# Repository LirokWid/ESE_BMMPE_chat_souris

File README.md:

# ESE_BMMPE_chat_souris

Ce project a pour but de développer un robot qui joue à chat avec d'autres robots, il embarque un PCB custom avec un STM32G070. Le projet est développé avec freeRTOS.

Le pcb permet la connection de :
- 2 moteurs DC
- 2 encodeurs
- 1 module Bluetooth
- 1 lidar ydlidar x4
- 4 capteurs de touche
- 2 capteurs de vide
- 1 centrale inertielle

Membres :

- M PICHERY
- B RODIER
- M VAN DE MOOSDJIK
- P.-E. RETAUX

## Organisation du code

Le code fonctionne en modules contenus dans le dossier `drivers`.
Les dossiers sont organisés de la manière suivante :

- `CONTROL` :
Gère la logique de contrôle du robot. Il génère les signaux de commande pour les moteurs et les encodeurs.
- `HC-05` :
Api de communication avec le module Bluetooth HC-05.
- `IT` :
Gère les interruptions du microcontrôleur.
- `LIDAR` : 
Routine d'acquisition des données du lidar.
- `MOTOR` :
Gère les moteurs et les encodeurs.
- `MPU6050` :
Api de communication avec la centrale inertielle MPU6050.
- `PARAMS` :
Gère les paramètres du robot.
- `SYS_HELPER` :
Fonctions utilitaires pour le système.
- `UART` :
Fonctions de communication UART.

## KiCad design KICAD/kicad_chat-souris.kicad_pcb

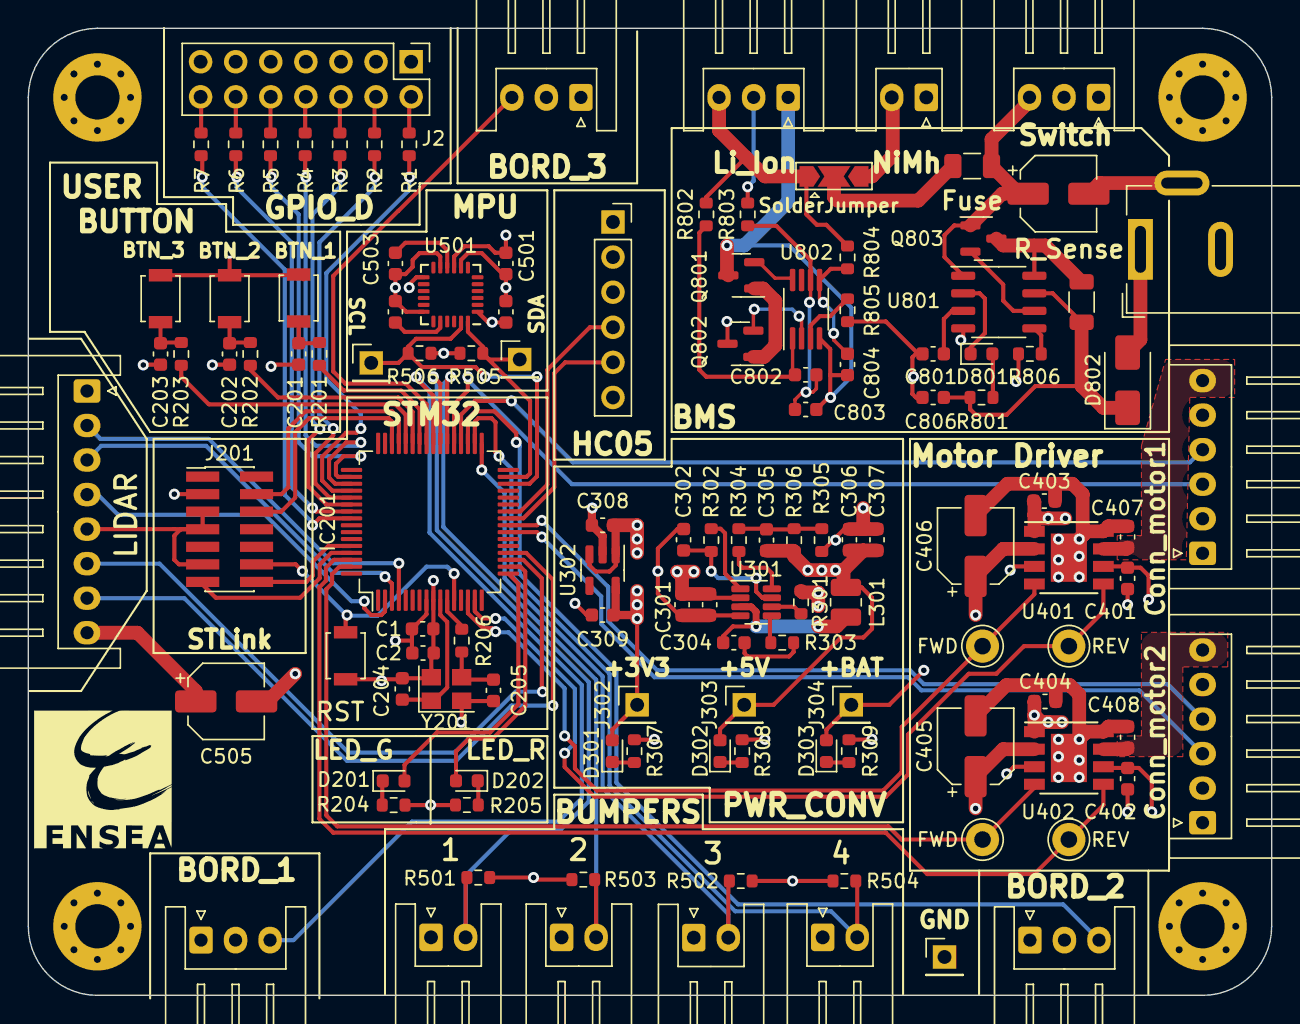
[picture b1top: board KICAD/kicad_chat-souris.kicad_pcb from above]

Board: 4 copper layers, 90.0 x 70.0 mm, 124 parts (1 on the bottom side), 98 nets.

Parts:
C1: 470n; C_0603_1608Metric
C2: 4.7µ; C_0603_1608Metric
C201, C202, C203, C302, C303, C304, C305, C503: 0.1uF; C_0603_1608Metric
C204, C205: 10pF; C_0603_1608Metric
C301, C306, C307: 22uF; C_0603_1608Metric
C308, C309, C401, C402: 1uF; C_0603_1608Metric
C403, C404, C407, C408: 47nF; C_0603_1608Metric
C405, C406: 10uF; CP_Elec_5x5.4
C501: 0.01nF; C_0603_1608Metric
C502: 0.01uF; C_0603_1608Metric
C504: 2.2nF; C_0603_1608Metric
C505: 4.7µ; CP_Elec_5x5.4
C801: 0.1µF; C_0603_1608Metric
C802, C803: 100n; C_0603_1608Metric
C804: 100nF; C_0603_1608Metric
C805: 10µ; CP_Elec_5x5.4
C806: 1µF; C_0603_1608Metric
D201: led_green; LED_0603_1608Metric
D202: led_red; LED_0603_1608Metric
D301, D302, D303: blue; LED_0603_1608Metric
D801: LED; LED_0603_1608Metric
D802: D_Schottky; D_SMA
F801: MF-NSML150/12-2; Fuse_1206_3216Metric
FWD: Pin_D1.0mm_L10.0mm_LooseFit
FWD#2: Pin_D1.0mm_L10.0mm_LooseFit
G1: LOGO; CHAT_SOURIE
IC201: STM32G070RBT6; LQFP-64_10x10mm_P0.5mm
J2: Conn_02x07_Counter_Clockwise; PinHeader_2x07_P2.54mm_Vertical
J201: ST/link connector; PinHeader_2x07_P1.27mm_Vertical_SMD
J301: power switch JST; JST_XH_S3B-XH-A_1x03_P2.50mm_Horizontal
J302: 3V3; PinHeader_1x01_P2.54mm_Vertical
J303: 5V; PinHeader_1x01_P2.54mm_Vertical
J304: V_BAT; PinHeader_1x01_P2.54mm_Vertical
J305: GND; PinHeader_1x01_P2.54mm_Vertical
J401: Conn_motor1; JST_XH_S6B-XH-A_1x06_P2.50mm_Horizontal
J402: Conn_motor2; JST_XH_S6B-XH-A_1x06_P2.50mm_Horizontal
J503: Conn_lidar; JST_XH_S8B-XH-A_1x08_P2.50mm_Horizontal
J504: Conn_Bmp_3; JST_XH_S2B-XH-A_1x02_P2.50mm_Horizontal
J505: Conn_Bmp_4; JST_XH_S2B-XH-A_1x02_P2.50mm_Horizontal
J506: SDA; PinHeader_1x01_P2.54mm_Vertical
J507: SCL; PinHeader_1x01_P2.54mm_Vertical
J601: Conn_bord1; JST_XH_S3B-XH-A_1x03_P2.50mm_Horizontal
J602: Conn_bord2; JST_XH_S3B-XH-A_1x03_P2.50mm_Horizontal
J801: 694102303002; BarrelJack_Wuerth_6941xx301002
J802: NiMH_Conn; JST_XH_S2B-XH-A_1x02_P2.50mm_Horizontal
J803: Li-Ion_Conn; JST_XH_S3B-XH-A_1x03_P2.50mm_Horizontal
JP801: SolderJumper; SolderJumper-3_P2.0mm_Open_TrianglePad1.0x1.5mm
L301: 4.7uH; L_1008_2520Metric
Q801, Q802: NMOS; SOT-23
Q803: PMOS; SOT-23
R1, R2, R3, R4, R5, R6, R7: R_Small; R_0603_1608Metric
R201, R202, R203: 20k; R_0603_1608Metric
R204: 5; R_0603_1608Metric
R205: 65; R_0603_1608Metric
R206: 10; R_0603_1608Metric
R301, R501, R502, R503, R504: 10k; R_0603_1608Metric
R302: 100k; R_0603_1608Metric
R303: 20; R_0603_1608Metric
R304: 16k; R_0603_1608Metric
R305: 7.68k; R_0603_1608Metric
R306: 40.2k; R_0603_1608Metric
R307, R802, R803, R804: 100; R_0603_1608Metric
R308: 50; R_0603_1608Metric
R309: 270; R_0603_1608Metric
R505, R506: 4.7k; R_0603_1608Metric
R801, R805: 2k; R_0603_1608Metric
R806: 19.6k; R_0603_1608Metric
REV: Pin_D1.0mm_L10.0mm_LooseFit
REV#2: Pin_D1.0mm_L10.0mm_LooseFit
R_SENSE801: 0.2; R_1206_3216Metric
SW201: RESET; SW_SPST_B3U-1000P
SW202: BTN_1; SW_SPST_B3U-1000P
SW203: BTN_2; SW_SPST_B3U-1000P
SW204: BTN_3; SW_SPST_B3U-1000P
U301: MP1475; SOT-23-8
U302: MIC5317-3.3v; SOT-23-5
U401: ZXBM5210-S_1; Diodes_SO-8EP
U402: ZXBM5210-S_2; Diodes_SO-8EP
U501: MPU-6050; InvenSense_QFN-24_4x4mm_P0.5mm
U701: PinSocket_1x06_P2.54mm_Vertical
U801: LTC1731ES8-8_4; SO-8_3.9x4.9mm_P1.27mm
U802: MSOP-8_3x3mm_P0.65mm
Y201: Crystal; Crystal_SMD_3225-4Pin_3.2x2.5mm
locked: Conn_Bmp_1; JST_XH_S2B-XH-A_1x02_P2.50mm_Horizontal
locked#2: Conn_Bmp_2; JST_XH_S2B-XH-A_1x02_P2.50mm_Horizontal
locked#3: Conn_bord3; JST_XH_S3B-XH-A_1x03_P2.50mm_Horizontal

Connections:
+3V3: C1.1, C2.1, C309.1, C401.1, C402.1, C501.1, C502.1, D301.2 (A), IC201.8 (VDD/VDDA), J201.3, J302.1, J401.5, J402.5, J601.2, J602.2, R501.2, R502.2, R503.2, R504.2, R505.2, R506.2, U302.5 (VOUT), U401.3 (VDD), U401.6 (VREF), U402.3 (VDD), U402.6 (VREF), U501.8 (VLOGIC), U501.13 (VDD), locked#3.2
+5V: C305.2, C306.1, C307.1, C308.1, C505.1, D302.2 (A), J303.1, J503.8, L301.2, R306.2, U302.1 (VIN), U302.3 (EN), U701.2 (Vcc(5v))
+BATT: C301.1, C303.1, C405.1, C406.1, D303.2 (A), J301.2, J304.1, R301.1, U301.2 (IN), U401.2 (VM), U402.2 (VM)
/Alimentation/BMS/Secu_Dout: Q801.2 (G), U802.8 (Dout)
/Alimentation/BMS/Secu_Sense: C804.1, R804.2, U802.5 (Sense)
/Alimentation/BMS/Secu_V-: R805.1, U802.3 (V-)
/Alimentation/BMS/Secu_VDD: C802.1, R802.1, U802.1 (VDD)
/Alimentation/BMS/Secu_Vc: C802.2, C803.1, R803.1, U802.6 (Vc)
/Alimentation/BMS/Secu_Vout: Q802.2 (G), U802.2 (Cout)
/Alimentation/BUCK_FB: R304.1, U301.8 (FB)
/Alimentation/BUCK_SW: C304.2, L301.1, U301.3 (SW)
/Drivers and motors connectors/ENCODER_1_A: IC201.37 (PA9), J401.3
/Drivers and motors connectors/ENCODER_1_B: IC201.36 (PA8), J401.4
/Drivers and motors connectors/ENCODER_2_A: IC201.23 (PA6), J402.3
/Drivers and motors connectors/ENCODER_2_B: IC201.24 (PA7), J402.4
/Drivers and motors connectors/MOT1_OUT1: C403.1, J401.1, U401.1 (OUT1)
/Drivers and motors connectors/MOT1_OUT2: C407.1, J401.6, U401.7 (OUT2)
/Drivers and motors connectors/MOT2_OUT1: C404.1, J402.1, U402.1 (OUT1)
/Drivers and motors connectors/MOT2_OUT2: C408.1, J402.6, U402.7 (OUT2)
/Drivers and motors connectors/MOTOR_1_FWD: FWD#2.1, IC201.14 (PC1), U401.4 (FWD)
/Drivers and motors connectors/MOTOR_1_REV: IC201.15 (PC2), REV#2.1, U401.5 (REV)
/Drivers and motors connectors/MOTOR_2_FWD: FWD.1, IC201.63 (PB9), U402.4 (FWD)
/Drivers and motors connectors/MOTOR_2_REV: IC201.62 (PB8), REV.1, U402.5 (REV)
/STM32/BTN_1: IC201.42 (PA10), R201.1
/STM32/BTN_2: IC201.43 (PA11_[PA9]), R202.1
/STM32/BTN_3: IC201.44 (PA12_[PA10]), R203.1
/STM32/Bordure_1: IC201.40 (PD8), J601.3
/STM32/Bordure_2: IC201.41 (PD9), J602.3
/STM32/Bordure_3: IC201.35 (PB15), locked#3.3
/STM32/Bumper_1: IC201.39 (PC7), R501.1, locked.2
/STM32/Bumper_2: IC201.38 (PC6), J504.2, R503.1
/STM32/Bumper_3: IC201.33 (PB13), R502.1, locked#2.2
/STM32/Bumper_4: IC201.34 (PB14), J505.2, R504.1
/STM32/I2C_SCL: IC201.30 (PB10), J507.1, R506.1, U501.23 (SCL)
/STM32/I2C_SDA: IC201.31 (PB11), J506.1, R505.1, U501.24 (SDA)
/STM32/LIDAR_MESURE_ENABLE: IC201.3 (PC13), J503.3
/STM32/LIDAR_MOTOR_ENABLE: IC201.4 (PC14-OSC32_IN), J503.2
/STM32/LIDAR_PWM: IC201.2 (PC12), J503.4
/STM32/NRST: IC201.12 (NRST), J201.12, SW201.2 (B)
/STM32/OSC_IN: C204.1, IC201.10 (PF0-OSC_IN), Y201.1
/STM32/OSC_OUT: IC201.11 (PF1-OSC_OUT), R206.1
/STM32/PD0: IC201.50 (PD0), R5.1
/STM32/PD1: IC201.51 (PD1), R4.1
/STM32/PD2: IC201.52 (PD2), R1.1
/STM32/PD3: IC201.53 (PD3), R2.1
/STM32/PD4: IC201.54 (PD4), R3.1
/STM32/PD5: IC201.55 (PD5), R6.1
/STM32/PD6: IC201.56 (PD6), R7.1
/STM32/SWCLK: IC201.46 (PA14-BOOT0), J201.6
/STM32/SWDIO: IC201.45 (PA13), J201.4
/STM32/USART1_RX: IC201.61 (PB7), J201.13
/STM32/USART1_TX: IC201.60 (PB6), J201.14
/STM32/USART2_RX: IC201.20 (PA3), J503.7
/STM32/USART2_TX: IC201.19 (PA2), J503.6
/STM32/USART3_RX: IC201.26 (PC5), U701.4 (Tx)
/STM32/USART3_TX: IC201.25 (PC4), U701.5 (Rx)
BAT+: C805.1, F801.1, J301.3, Q803.1 (D), U801.1 (BAT)
GND: C1.2, C2.2, C201.2, C202.2, C203.2, C204.2, C205.2, C301.2, C302.2, C303.2, C306.2, C307.2, C308.2, C309.2, C401.2, C402.2, C403.2, C404.2, C405.2, C406.2, C407.2, C408.2, C501.2, C502.2, C503.2, C504.2, C505.2, C801.2, C805.2, C806.2, IC201.9 (VSS/VSSA), J2.1, J2.3, J2.5, J2.7, J2.9, J2.11, J2.13, J201.5, J201.7, J201.11, J305.1, J401.2, J402.2, J503.5, J504.1, J505.1, J601.1, J602.1, J801.2, J801.3, J802.1, Q802.3 (S), R204.2, R205.1, R305.1, R307.2, R308.2, R309.2, R805.2, R806.2, SW201.1 (A), SW202.1 (A), SW203.1 (A), SW204.1 (A), U301.4 (GND), U302.2 (GND), U401.8 (GND), U401.9 (GND), U402.8 (GND), U402.9 (GND), U501.1 (CLKIN), U501.9 (AD0), U501.11 (FSYNC), U501.18 (GND), U701.3 (GND), U801.4 (GND), Y201.2, Y201.4, locked.1, locked#2.1, locked#3.1
Li_Ion+: J803.3, JP801.1 (A), R802.2, R804.1
Li_Ion-: C803.2, C804.2, J803.1, Q801.3 (S), U802.4 (VSS)
Li_Ion_INTER: J803.2, R803.2
unnamed: C205.1, R206.2, Y201.3
unnamed: C304.1, R303.2
unnamed: C305.1, R304.2, R305.2, R306.1
unnamed: D201.2 (A), IC201.17 (PA0)
unnamed: D201.1 (K), R204.1
unnamed: D202.2 (A), IC201.18 (PA1)
unnamed: D202.1 (K), R205.2
unnamed: D301.1 (K), R307.1
unnamed: D302.1 (K), R308.1
unnamed: D303.1 (K), R309.1
unnamed: D801.2 (A), R801.2
unnamed: D801.1 (K), U801.2 (*CHRG)
unnamed: C806.1, D802.1 (K), R801.1, R_SENSE801.1, U801.7 (VCC)
unnamed: J2.2, R1.2
unnamed: J2.4, R2.2
unnamed: J2.6, R3.2
unnamed: J2.8, R4.2
unnamed: J2.10, R5.2
unnamed: J2.12, R6.2
unnamed: J2.14, R7.2
unnamed: F801.2, JP801.2 (C)
unnamed: Q801.1 (D), Q802.1 (D)
unnamed: Q803.2 (G), U801.6 (DRV)
unnamed: Q803.3 (S), R_SENSE801.2, U801.8 (SENSE)
unnamed: C201.1, R201.2, SW202.2 (B)
unnamed: C202.1, R202.2, SW203.2 (B)
unnamed: C203.1, R203.2, SW204.2 (B)
unnamed: R303.1, U301.5 (BST)
unnamed: R301.2, U301.6 (EN/SYNC)
unnamed: R302.2, U301.1 (PG)
unnamed: C302.1, R302.1, U301.7 (VCC)
unnamed: C504.1, U501.20 (CPOUT)
unnamed: C503.1, U501.10 (REGOUT)
unnamed: R806.1, U801.5 (PROG)
unnamed: C801.1, U801.3 (TIMER)
NiMh+: J802.2, JP801.3 (B)
V_ALIM: D802.2 (A), J801.1

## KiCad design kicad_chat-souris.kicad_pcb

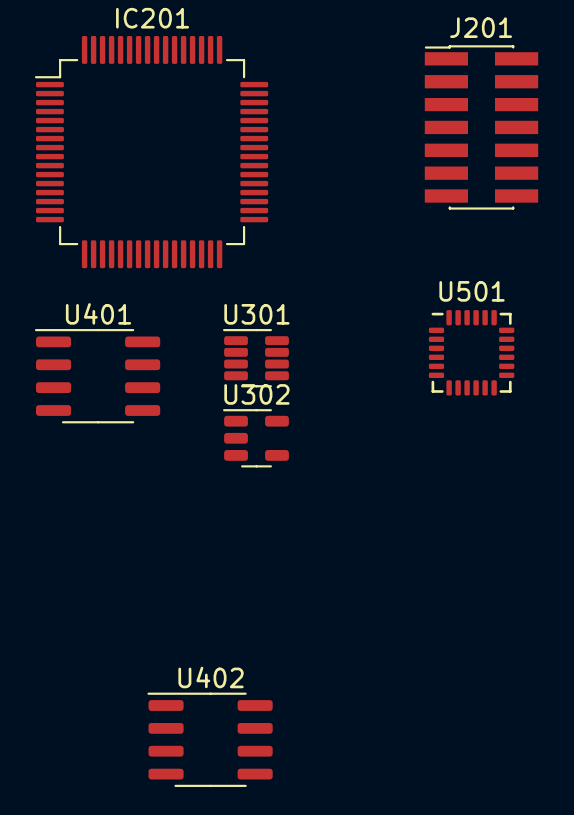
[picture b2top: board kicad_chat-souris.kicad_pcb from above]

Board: 2 copper layers, 7 parts (0 on the bottom side), 15 nets, no tracks yet.

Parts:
IC201: STM32G070RBT6; LQFP-64_10x10mm_P0.5mm
J201: ST/link connector; PinHeader_2x07_P1.27mm_Vertical_SMD
U301: MP1475; SOT-23-8
U302: MIC5317-3.3xM5; SOT-23-5
U401, U402: ZXBM5210-S; SOIC-8_3.9x4.9mm_P1.27mm
U501: MPU-6050; InvenSense_QFN-24_4x4mm_P0.5mm

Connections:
+3V3: IC201.8 (VDD/VDDA), U302.5 (VOUT), U401.3 (VDD), U401.6 (VREF), U402.3 (VDD), U402.6 (VREF), U501.8 (VLOGIC), U501.13 (VDD)
+5V: U302.1 (VIN), U302.3 (EN)
+BATT: U301.2 (IN), U401.2 (VM), U402.2 (VM)
/Drivers and motors connectors/MOTOR_1_FWD: IC201.14 (PC1), U401.4 (FWD)
/Drivers and motors connectors/MOTOR_1_REV: IC201.15 (PC2), U401.5 (REV)
/Drivers and motors connectors/MOTOR_2_FWD: IC201.63 (PB9), U402.4 (FWD)
/Drivers and motors connectors/MOTOR_2_REV: IC201.62 (PB8), U402.5 (REV)
/STM32/I2C_SCL: IC201.30 (PB10), U501.23 (SCL)
/STM32/I2C_SDA: IC201.31 (PB11), U501.24 (SDA)
/STM32/NRST: IC201.12 (NRST), J201.12
/STM32/SWCLK: IC201.46 (PA14-BOOT0), J201.6
/STM32/SWDIO: IC201.45 (PA13), J201.4
/STM32/USART1_RX: IC201.61 (PB7), J201.13
/STM32/USART1_TX: IC201.60 (PB6), J201.14
GND: IC201.9 (VSS/VSSA), J201.5, J201.7, J201.11, U301.4 (GND), U302.2 (GND), U401.8 (GND), U402.8 (GND), U501.1 (CLKIN), U501.9 (AD0), U501.11 (FSYNC), U501.18 (GND)

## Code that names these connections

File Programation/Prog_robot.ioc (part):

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Mcu.Name=STM32G070RBTx
Mcu.Package=LQFP64
Mcu.UserName=STM32G070RBTx
PA0.GPIOParameters=GPIO_Label
PA0.GPIO_Label=LED_STATE
PA0.Signal=GPIO_Output
PA1.GPIOParameters=GPIO_Label
PA1.GPIO_Label=LED_ERROR
PA1.Signal=GPIO_Output
PA10.GPIOParameters=GPIO_Label
PA10.GPIO_Label=BTN_1
PA10.Signal=GPXTI10
PA11\ [PA9].GPIOParameters=GPIO_Label
PA11\ [PA9].GPIO_Label=BTN_2
PA11\ [PA9].Signal=GPXTI11
PA12\ [PA10].GPIOParameters=GPIO_Label
PA12\ [PA10].GPIO_Label=BTN_3
PA12\ [PA10].Signal=GPXTI12
PA13.Mode=Serial_Wire
PA13.Signal=SYS_SWDIO
PA14-BOOT0.Mode=Serial_Wire
PA14-BOOT0.Signal=SYS_SWCLK
PA2.Mode=Asynchronous
PA2.Signal=USART2_TX
PA3.Mode=Asynchronous
PA3.Signal=USART2_RX
PA6.GPIOParameters=GPIO_Label
PA6.GPIO_Label=ENCODER_2_A
PA6.Signal=S_TIM3_CH1
PA7.GPIOParameters=GPIO_Label
PA7.GPIO_Label=ENCODER_2_B
PA7.Signal=S_TIM3_CH2
PA8.GPIOParameters=GPIO_Label
PA8.GPIO_Label=ENCODER_1_B
PA8.Signal=S_TIM1_CH1
PA9.GPIOParameters=GPIO_Label
PA9.GPIO_Label=ENCODER_1_A
PA9.Signal=S_TIM1_CH2
PB10.Mode=I2C
PB10.Signal=I2C2_SCL
PB11.Mode=I2C
PB11.Signal=I2C2_SDA
PB13.GPIOParameters=GPIO_Label
PB13.GPIO_Label=BORDURE_1
PB13.Signal=GPXTI13
PB14.GPIOParameters=GPIO_Label
PB14.GPIO_Label=BORDURE_2
PB14.Signal=GPXTI14
PB15.GPIOParameters=GPIO_Label
PB15.GPIO_Label=BORDURE_3
PB15.Signal=GPXTI15
PB6.Mode=Asynchronous
PB6.Signal=USART1_TX
PB7.Mode=Asynchronous
PB7.Signal=USART1_RX
PB8.GPIOParameters=GPIO_Label
PB8.GPIO_Label=MOTOR_2_REV
PB8.Signal=S_TIM16_CH1
PB9.GPIOParameters=GPIO_Label
PB9.GPIO_Label=MOTOR_2_FWD
PB9.Signal=S_TIM17_CH1
PC1.GPIOParameters=GPIO_Label
PC1.GPIO_Label=MOTOR_1_FWD
PC1.Signal=S_TIM15_CH1
PC12.GPIOParameters=GPIO_Label
PC12.GPIO_Label=LIDAR_PWM
PC12.Signal=S_TIM14_CH1
PC13.GPIOParameters=GPIO_Label
PC13.GPIO_Label=LIDAR_MOTOR_ENABLE
PC13.Signal=GPIO_Output
PC14-OSC32_IN\ (PC14).GPIOParameters=GPIO_Label
PC14-OSC32_IN\ (PC14).GPIO_Label=LIDAR_MESURE ENABLE
PC14-OSC32_IN\ (PC14).Signal=GPIO_Output
PC2.GPIOParameters=GPIO_Label
PC2.GPIO_Label=MOTOR_1_REV
PC2.Signal=S_TIM15_CH2
PC4.Mode=Asynchronous
PC4.Signal=USART3_TX
PC5.Mode=Asynchronous
PC5.Signal=USART3_RX
PC6.GPIOParameters=GPIO_Label
PC6.GPIO_Label=BUMPER_1
PC6.Signal=GPXTI6
PC7.GPIOParameters=GPIO_Label
PC7.GPIO_Label=BUMPER_2
PC7.Signal=GPXTI7
PD0.Signal=GPIO_Input
PD1.Signal=GPIO_Input
PD2.Signal=GPIO_Input
PD3.Signal=GPIO_Input
PD4.Signal=GPIO_Input
PD5.Signal=GPIO_Input
PD6.Signal=GPIO_Input
PD8.GPIOParameters=GPIO_Label
PD8.GPIO_Label=BUMPER_3
PD8.Signal=GPXTI8
PD9.GPIOParameters=GPIO_Label
PD9.GPIO_Label=BUMPER_4
PD9.Signal=GPXTI9
PF0-OSC_IN\ (PF0).Mode=HSE-External-Oscillator
PF0-OSC_IN\ (PF0).Signal=RCC_OSC_IN
PF1-OSC_OUT\ (PF1).Mode=HSE-External-Oscillator
PF1-OSC_OUT\ (PF1).Signal=RCC_OSC_OUT
RCC.HSE_VALUE=8000000
RCC.SYSCLKFreq_VALUE=16000000
board=custom

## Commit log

2023-09-25 Kicad first rev schematics
2023-09-28 update file structure
2023-09-28 update schematics
2023-10-05 Completed schematics
2023-10-05 added CUBE IDE project
2023-10-05 update polarity connectors
2023-10-05 lidar driver project added
2023-10-26 PCB finalized
2023-10-26 README updated
2023-11-30 modified prog robot to an empty freeRTOS project
2023-12-06 first version HC05 functions
2023-12-06 set interruption to read from USART3 (bluetooth module)
2023-12-07 speed setting fonctions v1
2023-12-07 test2: ramp of speed (no blocking)
2023-12-13 multiple add + new projects
2023-12-21 Motor driving - 21.12.2023 10 AM
2024-01-07 Lidar tracking works
2024-01-07 added processing 2d render of lidar data
2024-01-08 changelent pres vacances
2024-01-08 udate tracking
2024-01-12 Update v1
2024-01-18 code and readme update
2024-03-19 Update project description and member names
